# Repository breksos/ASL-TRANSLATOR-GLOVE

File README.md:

# ASL Sign Language Glove Translator

**GTU CSE496 Graduation Project** — Berk Hakan ÖGE & Utku GÖKÇEK, May–June 2026.

A wearable smart glove that recognises American Sign Language (ASL) gestures
and translates them into spoken text in real time. The user wears the glove,
performs a sign, and a Flutter mobile app speaks the translated word aloud
via TTS.

For the original project brief see [GLOVE_PROJECT.md](GLOVE_PROJECT.md).

---

## Repository layout

```
ASL/
├── README.md                ← you are here
├── GLOVE_PROJECT.md         original brief / spec
│
├── firmware/                ESP32 firmware (sender + receiver + diagnostics)
│   ├── arduino/             Arduino IDE .ino sketches (primary development path)
│   └── idf/                 ESP-IDF projects (parallel alternative; same logic)
│
├── hardware/
│   └── ASL_Glove/           KiCad PCB design for the prototype board
│
├── flutter_app/             Mobile app — BLE receive + TFLite inference + TTS
│
├── scripts/                 Python tooling
│   ├── record.py            primary data-recording UI
│   ├── strip_palm.py        create no-palm variant of dataset
│   └── diagnostics/         link-quality and sensor-health diagnostics
│       ├── sniff.py
│       ├── palm_check.py
│       ├── motion_check.py
│       ├── long_check.py
│       ├── long_csv_check.py
│       ├── soak_30min.py
│       └── inspect.py
│
├── data/                    labelled training samples (with palm channels)
├── data_nopalm/             same samples, palm stripped (45 channels)
│
└── docs/
    ├── datasheets/          part datasheets (MPU6050, ESP32-C3, etc.)
    └── images/              project photos, diagrams
```

---

## System architecture

```
┌─────────────────────────────────────────────────────────────────────┐
│                              The Glove                              │
│                                                                     │
│  ┌────────┐  ┌────────┐  ┌────────┐  ┌────────┐  ┌────────┐         │
│  │ thumb  │  │ index  │  │ middle │  │  ring  │  │ pinky  │         │
│  │ XIAO+  │  │ XIAO+  │  │ XIAO+  │  │ XIAO+  │  │ XIAO+  │         │
│  │ MPU6050│  │ MPU6050│  │ MPU6050│  │ MPU6050│  │ MPU6050│         │
│  └───┬────┘  └───┬────┘  └───┬────┘  └───┬────┘  └───┬────┘         │
│      │ ESP-NOW broadcast, channel 11, 50 Hz, dup-send               │
│      └────────────┬───────────┴───────────┴───────────┘             │
│                   ▼                                                 │
│         ┌────────────────────┐                                      │
│         │  ESP32 DevKit1     │                                      │
│         │  (back of wrist)   │                                      │
│         └─────┬──────────────┘                                      │
└───────────────┼─────────────────────────────────────────────────────┘
                │
                │  USB Serial (CSV) for recording sessions
                │  OR
                │  BLE GATT notify (45 floats × 50 Hz) for phone
                ▼
        ┌───────────────┐               ┌──────────────────────┐
        │   record.py   │               │   Flutter app        │
        │  (laptop)     │               │   (Android phone)    │
        │   → CSV files │               │   TFLite + TTS       │
        └───────┬───────┘               └──────────────────────┘
                ▼
        ┌──────────────────┐
        │  Edge Impulse    │
        │  CNN training    │
        │  → .tflite       │
        └──────────────────┘
                │
                └────────────► flutter_app/assets/models/
```

---

## Quick-start by role

### "I want to flash the firmware"

```sh
# Arduino — primary path
cd firmware/arduino
# Open the project you want in Arduino IDE 2.x (e.g. asl_finger_sender)
# Set FINGER_ID 1..5 per board, flash to each XIAO ESP32-C3
# Flash asl_hand_receiver to the DevKit1
```

Details: see [firmware/arduino/README.md](firmware/arduino/README.md).

For the IDF equivalent: see [firmware/idf/README.md](firmware/idf/README.md).

### "I want to record training data"

```sh
pip install pyserial
python scripts/record.py --port COM15 --label A
```

Press SPACE to record a sample, type a letter to change label, q to quit.
Saves `data/<label>/<label>_NNN.csv`. See `python scripts/record.py --help`.

### "I want to diagnose link health"

```sh
# Quick 20 s per-source rate + max gap
python scripts/diagnostics/palm_check.py

# 30 s while the user signs — checks for motion-induced loss
python scripts/diagnostics/motion_check.py

# 30 min passive soak — checks thermal/firmware stability
python scripts/diagnostics/soak_30min.py

# 5 min CSV-mode soak (asl_csv_logger firmware)
python scripts/diagnostics/long_csv_check.py
```

### "I want to train a model"

1. Record dataset to `data/<label>/*.csv` via `record.py`
2. (Optional) Strip palm channels: `python scripts/strip_palm.py` produces `data_nopalm/`
3. Upload to Edge Impulse with `edge-impulse-uploader --category split --label <X> data/<X>/*.csv` per class
4. Configure impulse: window 2000 ms, stride 500 ms, 50 Hz, **Raw Data**, **Classification (Keras)**
5. Normalize features: **scikit-learn StandardScaler**
6. Use the 1D CNN architecture (see `flutter_app/README.md` for the Keras code)
7. Train, evaluate on Model Testing tab
8. Deployment → TensorFlow Lite → download

### "I want to run the mobile app"

See [flutter_app/README.md](flutter_app/README.md) for full setup. The summary:

1. `cd flutter_app && flutter create --org com.gtu.aslglove --project-name asl_glove .`
2. Drop `asl-letters.tflite`, `asl-words.tflite` + labels into `assets/models/`
3. Drop normalization `stats.json` into `assets/normalization/`
4. `flutter run`

---

## Project status checklist

| Component | Status |
|---|---|
| Sender firmware (Arduino + IDF) | ✅ working, current |
| Receiver firmware (USB CSV path) | ✅ working |
| Receiver firmware (BLE bridge for phone) | ⏳ pending |
| Data recorder (`record.py`) | ✅ working |
| Diagnostic scripts | ✅ working |
| Smoke dataset (5 signs × 30) | ✅ collected |
| Smoke model (1D CNN, no-palm) | ✅ 87.7 % test accuracy |
| Letter dataset (A–Z × 60, multi-session) | ⏳ pending |
| Word dataset (15–20 signs × 60) | ⏳ pending |
| Flutter app skeleton | ✅ written, awaiting model file |
| Trie disambiguation engine | ⏳ pending |

---

## Key engineering decisions

- **Distributed ESP-NOW**, not a wired I2C mux — each finger XIAO transmits independently. Eliminates long wires across joints.
- **Channel 11**, not the default channel 6 — local 2.4 GHz neighbours saturate channel 6.
- **Duplicate-send on every sender** — each packet broadcast twice 800 µs apart. Receiver dedupes by `seq`. Roughly squares the loss rate.
- **External U.FL antennas** instead of the XIAO's PCB chip antenna — measured 10–15× link-loss improvement.
- **Palm MPU dropped** after A/B testing showed identical overall accuracy and *improved* NO class F1 without it. 45-channel input instead of 54.
- **1D CNN architecture**, not the default MLP — boosted test accuracy from 55 % to 88 % on fresh recordings.
- **Mobile-side ML** — ESP32 lacks compute for real-time CNN; phone runs the model.

---

## Open tasks (high-level)

Tracked in detail in the project's task list. Headline items:

1. Reassemble the glove with brick-pattern antenna layout + tight compression glove + clean power distribution
2. Multi-session data collection (4 sessions × 15 samples per sign)
3. Train production Letters and Words models
4. Add BLE GATT server to receiver firmware
5. Implement Trie engine for U/V, M/N, S/T disambiguation in letter mode

---

## License

Academic project, GTU CSE496. Use is permitted for educational reference;
contact authors for commercial use.

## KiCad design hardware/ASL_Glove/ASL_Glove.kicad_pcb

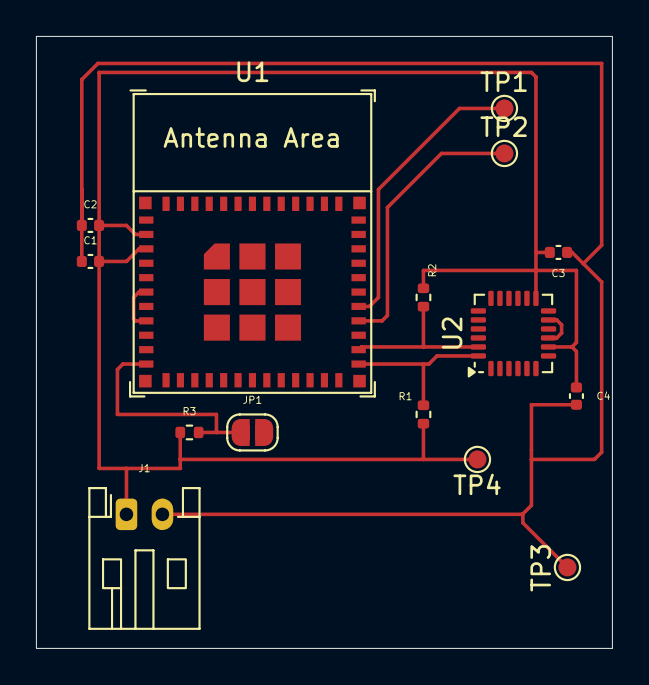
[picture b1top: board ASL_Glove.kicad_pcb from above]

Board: 2 copper layers, 32.0 x 34.0 mm, 15 parts (0 on the bottom side), 7 nets.

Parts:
C1, C3, C4: 100nF; C_0402_1005Metric
C2: 10uF; C_0402_1005Metric
J1: Conn_01x02; JST_PH_S2B-PH-K_1x02_P2.00mm_Horizontal
JP1: ROLE_SEL; SolderJumper-2_P1.3mm_Open_RoundedPad1.0x1.5mm
R1, R2: 4.7k; R_0402_1005Metric
R3: 10k; R_0402_1005Metric
TP1: TX; TestPoint_Pad_D1.0mm
TP2: RX; TestPoint_Pad_D1.0mm
TP3: GND; TestPoint_Pad_D1.0mm
TP4: 3V3; TestPoint_Pad_D1.0mm
U1: ESP32-C3-MINI-1
U2: MPU-6050; InvenSense_QFN-24_4x4mm_P0.5mm

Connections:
+3V3: C1.2, C2.2, C3.2, C4.1, J1.1, R1.1, R2.1, R3.1, TP4.1 (1_1), U1.2 (3V3), U1.3 (3V3), U2.8 (VLOGIC), U2.13 (VDD)
GND: C1.1, C2.1, C3.1, C4.2, J1.2, JP1.2 (B), TP3.1 (1_1), U1.1 (GND), U1.6 (GND), U1.8 (GND), U1.12 (GND), U1.15 (GND), U1.16 (GND), U1.19 (GND), U1.24 (GND), U1.27 (GND), U1.30 (GND), U2.9 (AD0), U2.11 (FSYNC), U2.18 (GND)
unnamed: JP1.1 (A), R3.2, U1.11 (IO10)
unnamed: R1.2, U1.25 (IO8), U2.24 (SDA)
unnamed: R2.2, U1.26 (IO9), U2.23 (SCL)
unnamed: TP2.1 (1_1), U1.28 (RX)
unnamed: TP1.1 (1_1), U1.29 (TX)

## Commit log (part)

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2026-06-14 final ver
